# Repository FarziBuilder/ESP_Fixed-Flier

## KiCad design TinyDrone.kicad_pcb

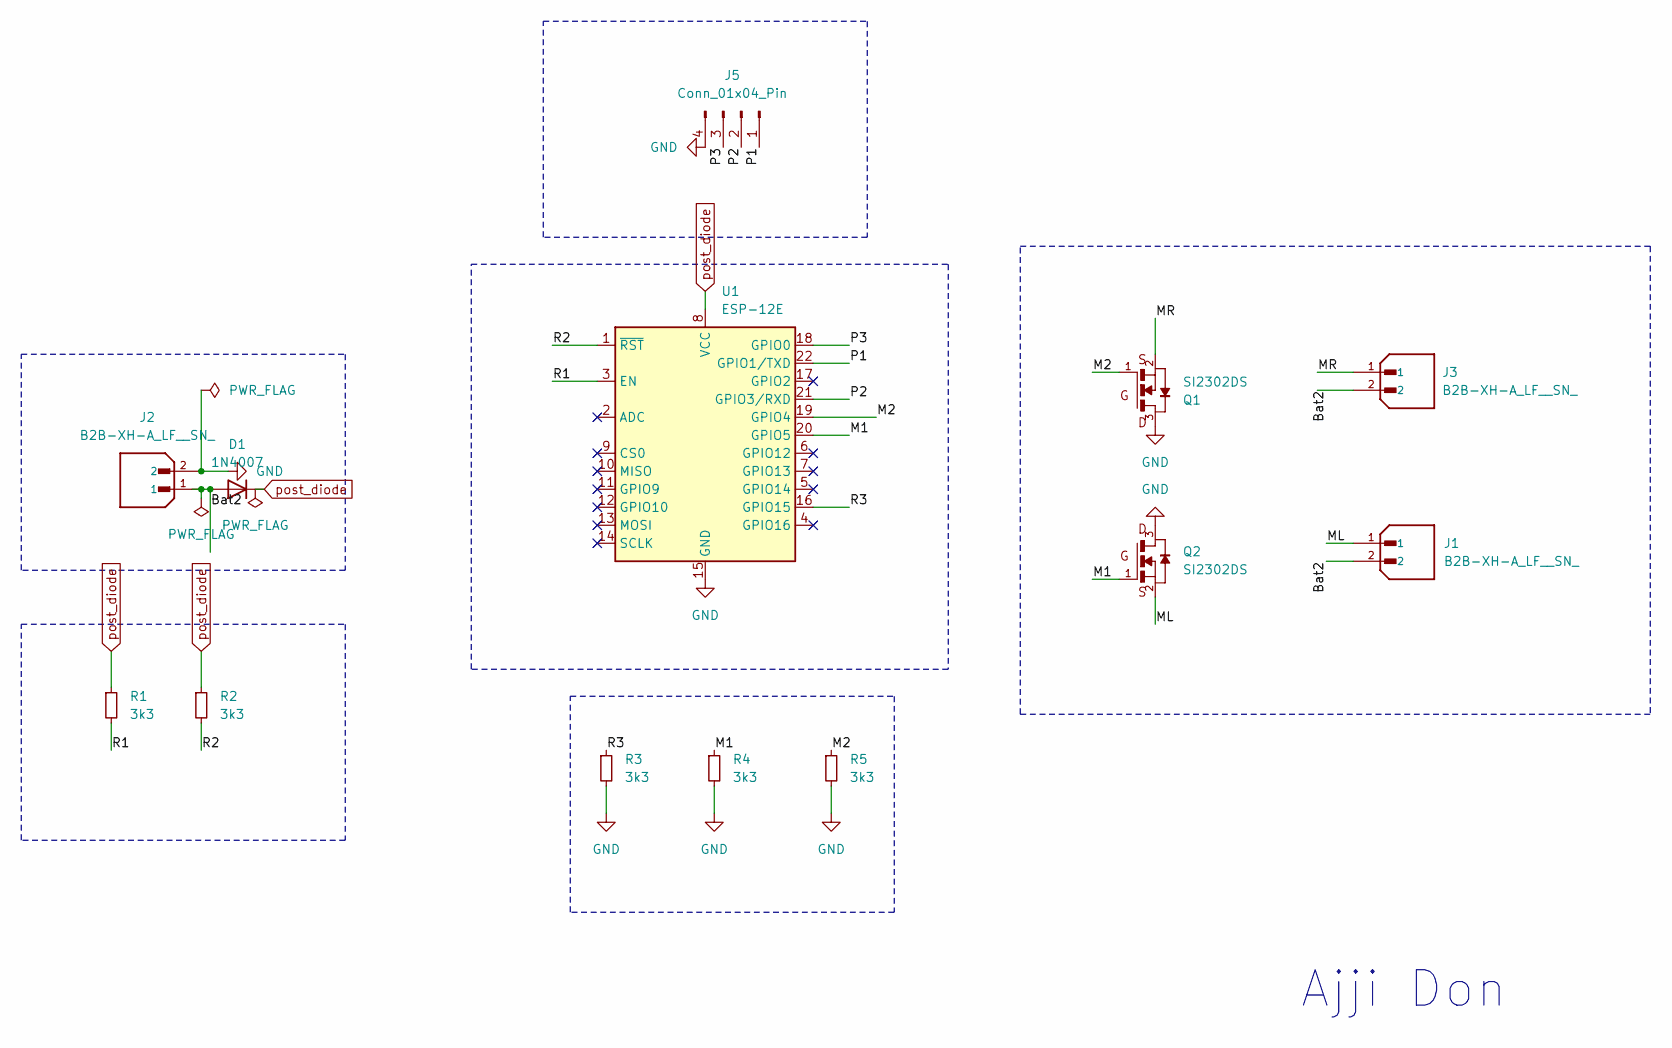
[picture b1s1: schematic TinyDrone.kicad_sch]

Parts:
D1: 1N4007; D_DO-41_SOD81_P10.16mm_Horizontal
J1, J2, J3: B2B-XH-A_LF__SN_; JST_B2B-XH-A_LF__SN_; PARTREV N/A
J5: Conn_01x04_Pin; FanPinHeader_1x04_P2.54mm_Vertical
Q1, Q2: SI2302DS; SOT23-3_TO-236AB
R1, R2, R3, R4, R5: 3k3; R_0603_1608Metric_Pad0.98x0.95mm_HandSolder
U1: ESP-12E

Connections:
/Bat2: D1.2 (A), J1.2, J2.1, J3.2
/M1: Q2.1, R4.1, U1.20 (GPIO5)
/M2: Q1.1, R5.1, U1.19 (GPIO4)
/ML: J1.1, Q2.2
/MR: J3.1, Q1.2
/P1: J5.1, U1.22 (GPIO1/TXD)
/P2: J5.2, U1.21 (GPIO3/RXD)
/P3: J5.3, U1.18 (GPIO0)
/R1: R1.2, U1.3 (EN)
/R2: R2.2, U1.1 (~RST)
/R3: R3.1, U1.16 (GPIO15)
GND: J2.2, J5.4, Q1.3, Q2.3, R3.2, R4.2, R5.2, U1.15 (GND)
post_diode: D1.1 (K), R1.1, R2.1, U1.8 (VCC)

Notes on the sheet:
Ajji Don

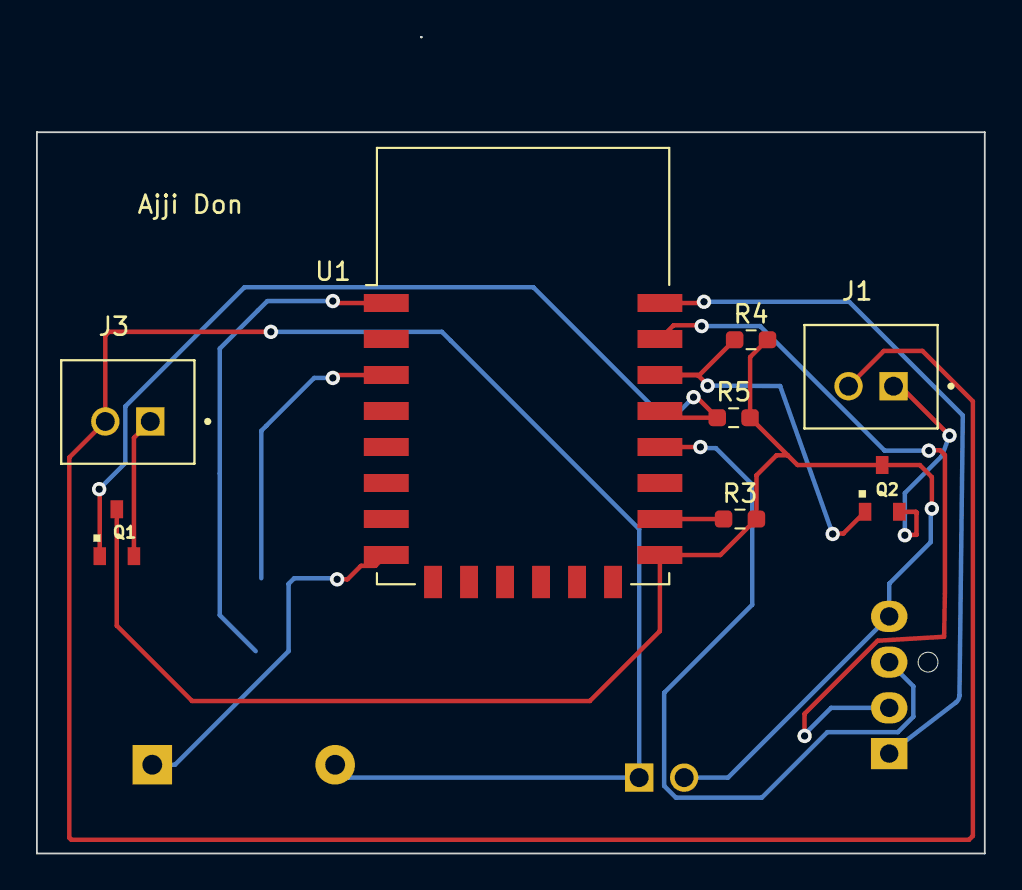
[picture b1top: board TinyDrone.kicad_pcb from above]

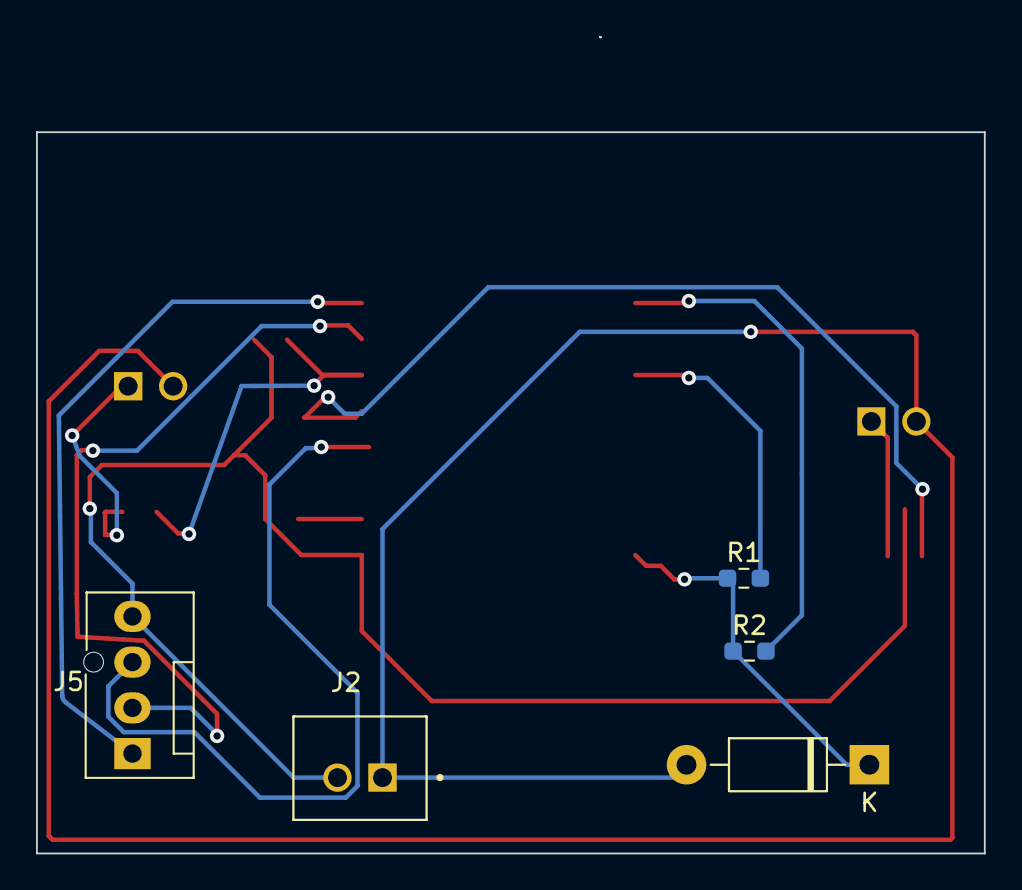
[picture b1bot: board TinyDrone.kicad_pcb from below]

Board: 2 copper layers, 52.7 x 45.4 mm, 13 parts (5 on the bottom side), 13 nets.
